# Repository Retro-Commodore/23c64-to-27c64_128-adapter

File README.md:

# RCEU2305 - 23C64 to 27C64/27C128 ROM to EPROM adapter
A 23C64 ROM to 27C64/27C128 adapter

Meaning you can add a 27C64 or 27C128 eprom to the adapter, and plug the adapter into one of the rom sockets of i.e. the C64, C128 etc.

To use a 27C64, you only need a 28pin socket and 2 x 12pin male/male sil headers, preferably turned/tulip style.

You can make the adapter into a dual rom, by a 27C128 eprom, a 4k7 - 10k ohm resistor, a wire with a 2 way switch connected to the 2 pin header. This will make you able to switch between 2 roms (each 8kB) in the 16kB eprom. 

You can also use this pcb to create an adapter to read the ROM chips in the C64, simply add 2x14pin male/male sil headers in the bottom instead of the 28pin rom socket. and 24pin rom socket on top instead of the 2x12 pin sil headers in the bottom. Basically swap posistions of the socket and the sil haaders.

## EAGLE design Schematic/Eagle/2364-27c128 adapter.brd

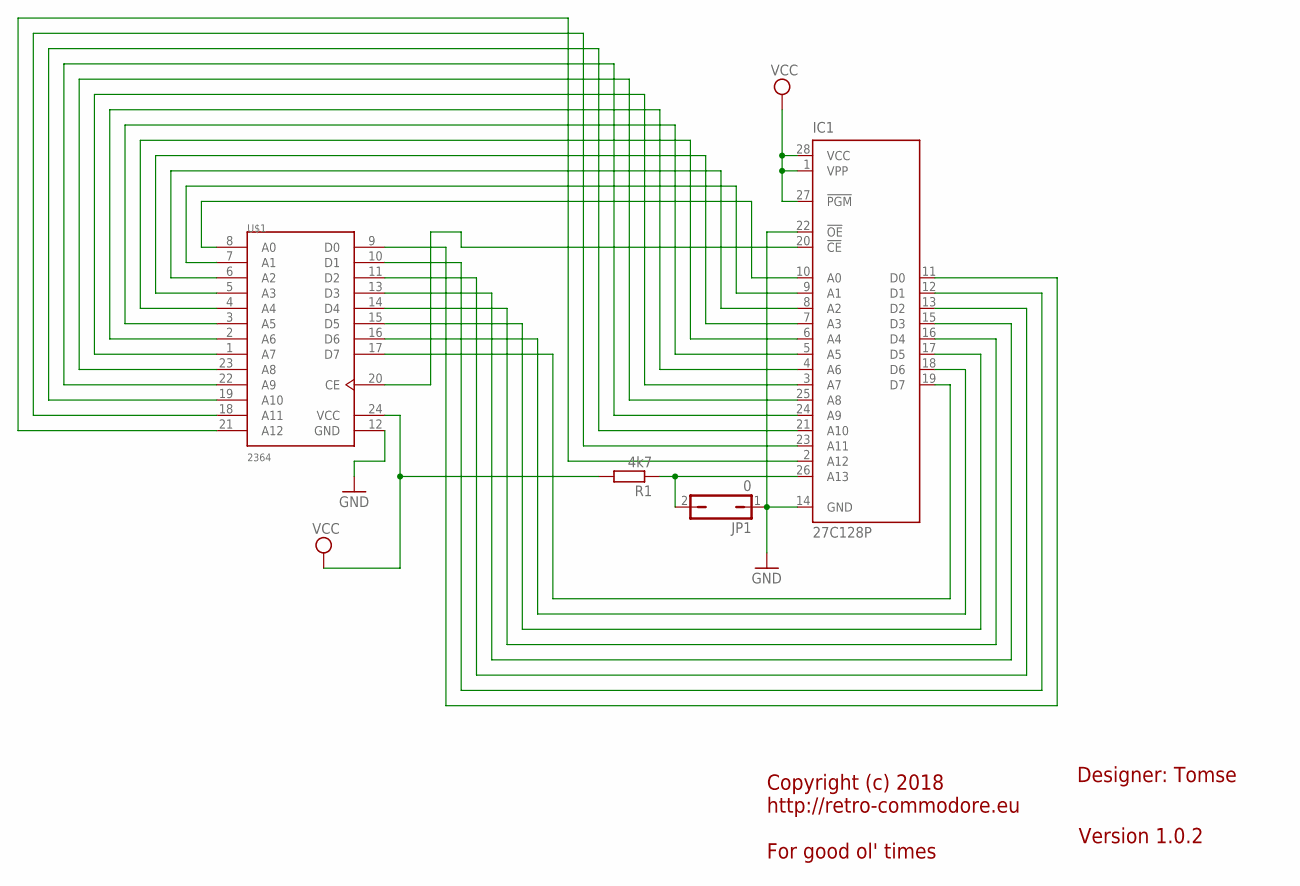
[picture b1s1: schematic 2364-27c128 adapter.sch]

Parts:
IC1: 27C128P; DIL28-6
JP1: 0; JP1
R1: 4k7; 0207/12
U$1: 2364; DIP24

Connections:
GND: IC1.14 (GND), IC1.22 (!OE), JP1.1, U$1.12 (GND)
unnamed: IC1.10 (A0), U$1.8 (A0)
unnamed: IC1.9 (A1), U$1.7 (A1)
unnamed: IC1.8 (A2), U$1.6 (A2)
unnamed: IC1.7 (A3), U$1.5 (A3)
unnamed: IC1.6 (A4), U$1.4 (A4)
unnamed: IC1.5 (A5), U$1.3 (A5)
unnamed: IC1.4 (A6), U$1.2 (A6)
unnamed: IC1.3 (A7), U$1.1 (A7)
unnamed: IC1.25 (A8), U$1.23 (A8)
unnamed: IC1.24 (A9), U$1.22 (A9)
unnamed: IC1.21 (A10), U$1.19 (A10)
unnamed: IC1.23 (A11), U$1.18 (A11)
unnamed: IC1.2 (A12), U$1.21 (A12)
unnamed: IC1.19 (D7), U$1.17 (D7)
unnamed: IC1.18 (D6), U$1.16 (D6)
unnamed: IC1.17 (D5), U$1.15 (D5)
unnamed: IC1.16 (D4), U$1.14 (D4)
unnamed: IC1.15 (D3), U$1.13 (D3)
unnamed: IC1.13 (D2), U$1.11 (D2)
unnamed: IC1.12 (D1), U$1.10 (D1)
unnamed: IC1.11 (D0), U$1.9 (D0)
unnamed: IC1.20 (!CE), U$1.20 (CE)
unnamed: IC1.26 (A13), JP1.2, R1.1
VCC: IC1.1 (VPP), IC1.27 (!PGM), IC1.28 (VCC), R1.2, U$1.24 (VCC)

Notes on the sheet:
Copyright (c) 2018 http://retro-commodore.eu For good ol' times
Version 1.0.2
Designer: Tomse

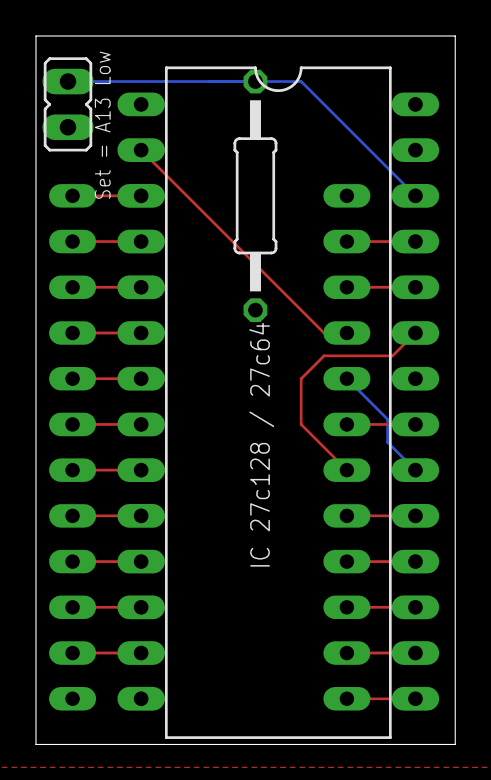
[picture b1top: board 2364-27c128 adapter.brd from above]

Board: 2 copper layers, 23.3 x 39.4 mm, 4 parts (0 on the bottom side), 25 nets.

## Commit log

2018-10-09 Update LICENSE
2020-04-06 Cosmetic changes

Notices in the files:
Schematic/Eagle/2364-27c128 adapter.brd:
Copyright (c) 2018-2020
